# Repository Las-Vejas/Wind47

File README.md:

# Wind47

This is a 60% Ortho linear keyboard, made with Gateron low profile red switches, sk6812mini leds, 2 rotary encoders and a RP2040 Pro Micro.
The keyboard uses a sandwich case, and will probably use QMK for software, but i will do that when i assemble the keyboard.

I made this project to try out making a keyboard, and i wanted to try out an ortholinear keyboard.

I couldn't find a 2U keycap anywhere and im just so done :sob:

## PCB

## Schematic

## Case

- Bottom

- Middle plate

- Top frame

## BOM

| **Quantity** | **Value**                        | **Price** | **Link**                                                                                                                                                                                                                                                                                                                                                                                                                                                                                                                                                                                                                                                                                                                                               |
| ------------ | -------------------------------- | --------- | ------------------------------------------------------------------------------------------------------------------------------------------------------------------------------------------------------------------------------------------------------------------------------------------------------------------------------------------------------------------------------------------------------------------------------------------------------------------------------------------------------------------------------------------------------------------------------------------------------------------------------------------------------------------------------------------------------------------------------------------------------ |
| 5            | Pcb                              | $12.50    | N/A                                                                                                                                                                                                                                                                                                                                                                                                                                                                                                                                                                                                                                                                                                                                                    |
| 47           | Gateron Low Profile Red Switches | $19.10    | [Link](https://www.aliexpress.com/item/1005006870413847.html?spm=a2g0o.cart.0.0.390838daOVG1qw&mp=1&pdp_npi=5%40dis%21USD%21USD%2019.14%21USD%2013.14%21%21USD%2013.14%21%21%21%40211b441e17518077163774247e0c39%2112000038574465209%21ct%21LT%216401819456%21%211%210)                                                                                                                                                                                                                                                                                                                                                                                                                                                                                |
| 47           | Hot Swap Socket                  | $7.21     | [Link](https://www.aliexpress.com/item/1005006042596309.html?spm=a2g0o.detail.0.0.4591LRi5LRi5tJ&mp=1&pdp_npi=5%40dis%21USD%21USD%207.21%21USD%207.21%21%21USD%207.21%21%21%21%40211b441e17518077556815067e0c39%2112000036713923613%21ct%21LT%216401819456%21%211%210)                                                                                                                                                                                                                                                                                                                                                                                                                                                                                 |
| 47           | SK6812MINI LED                   | $3.73     | [Link](https://www.aliexpress.com/item/1005007863635868.html?spm=a2g0o.detail.pcDetailTopMoreOtherSeller.1.677c0nRO0nRO4E&gps-id=pcDetailTopMoreOtherSeller&scm=1007.40050.354490.0&scm_id=1007.40050.354490.0&scm-url=1007.40050.354490.0&pvid=7b6b9416-d88f-40ac-8c6e-72acea23db31&_t=gps-id:pcDetailTopMoreOtherSeller,scm-url:1007.40050.354490.0,pvid:7b6b9416-d88f-40ac-8c6e-72acea23db31,tpp_buckets:668%232846%238113%231998&isseo=y&pdp_ext_f=%7B%22order%22%3A%2258%22%2C%22eval%22%3A%221%22%2C%22sceneId%22%3A%2230050%22%7D&pdp_npi=4%40dis%21USD%213.75%210.99%21%21%213.75%210.99%21%40211b441e17518085375406647e0c46%2112000042594617264%21rec%21LT%216401819456%21ABX&utparam-url=scene%3ApcDetailTopMoreOtherSeller%7Cquery_from%3A) |
| 47           | Diode                            | $1.27     | [Link](https://www.aliexpress.com/item/1005001994794541.html?spm=a2g0o.productlist.main.5.79744b32TWA3jy&aem_p4p_detail=202507060631334743561696551950005639918&algo_pvid=b71027a4-f8cb-4626-8b6c-0d46e56db36f&algo_exp_id=b71027a4-f8cb-4626-8b6c-0d46e56db36f-4&pdp_ext_f=%7B%22order%22%3A%2248%22%2C%22eval%22%3A%221%22%7D&pdp_npi=4%40dis%21USD%211.27%210.99%21%21%211.27%210.99%21%40210156fc17518086930522579eadfd%2112000018351925967%21sea%21LT%216401819456%21ABX&curPageLogUid=3FtGMGt9pZRI&utparam-url=scene%3Asearch%7Cquery_from%3A&search_p4p_id=202507060631334743561696551950005639918_5)                                                                                                                                           |
| 4            | Heatsets                         | $4.01     | [Link](https://www.aliexpress.com/item/1005006838108683.html?spm=a2g0o.cart.0.0.624d38daOi8uPh&mp=1&pdp_npi=5%40dis%21USD%21USD%204.01%21USD%204.01%21%21USD%204.01%21%21%21%40210384cc17518107729603022ec270%2112000038467725089%21ct%21LT%216401819456%21%211%210)                                                                                                                                                                                                                                                                                                                                                                                                                                                                                   |
| 4            | M2.5 x 16 mm screws              | $2.92     | [Link](https://www.aliexpress.com/item/32981974171.html)                                                                                                                                                                                                                                                                                                                                                                                                                                                                                                                                                                                                                                                                                               |
| 2            | RP2040 pro micro                 | $7.08     | [Link](https://www.aliexpress.com/item/1005006130019224.html?spm=a2g0o.cart.0.0.390838daOVG1qw&mp=1&pdp_npi=5%40dis%21USD%21USD%2010.73%21USD%203.54%21%21USD%203.54%21%21%21%40211b441e17518077163774247e0c39%2112000036037945376%21ct%21LT%216401819456%21%211%210)                                                                                                                                                                                                                                                                                                                                                                                                                                                                                  |
| 2            | Rotary Encoder Switch            | $4.02     | [Link](https://www.aliexpress.com/item/32976046900.html?spm=a2g0o.productlist.main.2.6d135ce9p75b8O&algo_pvid=2f2f8c8d-437f-418a-a9cf-3a8994fca321&algo_exp_id=2f2f8c8d-437f-418a-a9cf-3a8994fca321-1&pdp_ext_f=%7B%22order%22%3A%22312%22%2C%22eval%22%3A%221%22%7D&pdp_npi=4%40dis%21USD%214.02%210.99%21%21%214.02%210.99%21%402101062a17518079672848005e14be%2112000025499862671%21sea%21LT%216401819456%21ABX&curPageLogUid=TwSwWdvRutr6&utparam-url=scene%3Asearch%7Cquery_from%3A)                                                                                                                                                                                                                                                              |
| 1            | Keycaps                          | $14.31    | [Link](https://www.aliexpress.com/item/1005004870848679.html?spm=a2g0o.productlist.main.2.20d9kf7mkf7mCx&aem_p4p_detail=2025070606492214374909919118320005194176&algo_pvid=3430a230-6ff9-43e3-a2aa-89966d072dba&algo_exp_id=3430a230-6ff9-43e3-a2aa-89966d072dba-&pdp_ext_f=%7B%22order%22%3A%22302%22%2C%22eval%22%3A%221%22%7D&pdp_npi=4%40dis%21USD%2120.44%2112.07%21%21%2120.44%2112.07%21%40212e509017518097624981576eebc9%2112000033197803002%21sea%21LT%216401819456%21ABX&curPageLogUid=7uruuKe2d5zy&utparam-url=scene%3Asear)                                                                                                                                                                                                                |
| 1            | 2U Stabiliser                    | $2.61     | [Link](https://www.aliexpress.com/item/32864782721.html?spm=a2g0o.cart.0.0.667c38dabvmiJP&mp=1&pdp_npi=5%40dis%21USD%21USD%202.61%21USD%202.61%21%21USD%202.61%21%21%21%40210384cc17518106501267688ec270%2112000033338375131%21ct%21LT%216401819456%21%211%210)                                                                                                                                                                                                                                                                                                                                                                                                                                                                                        |
| 1            | Hex wrench                       | $2.47     | [Link](https://www.aliexpress.com/item/1005005430749401.html?spm=a2g0o.cart.0.0.624d38daOi8uPh&mp=1&pdp_npi=5%40dis%21USD%21USD%207.28%21USD%202.47%21%21USD%202.47%21%21%21%402103849717518141207421645eadef%2112000033040817269%21ct%21LT%216401819456%21%211%210)                                                                                                                                                                                                                                                                                                                                                                                                                                                                                   |
|              | **Total:**                       | $88.68    |                                                                                                                                                                                                                                                                                                                                                                                                                                                                                                                                                                                                                                                                                                                                                        |
|              | Aliexpress Shipping              | $7.45     | N/A                                                                                                                                                                                                                                                                                                                                                                                                                                                                                                                                                                                                                                                                                                                                                    |

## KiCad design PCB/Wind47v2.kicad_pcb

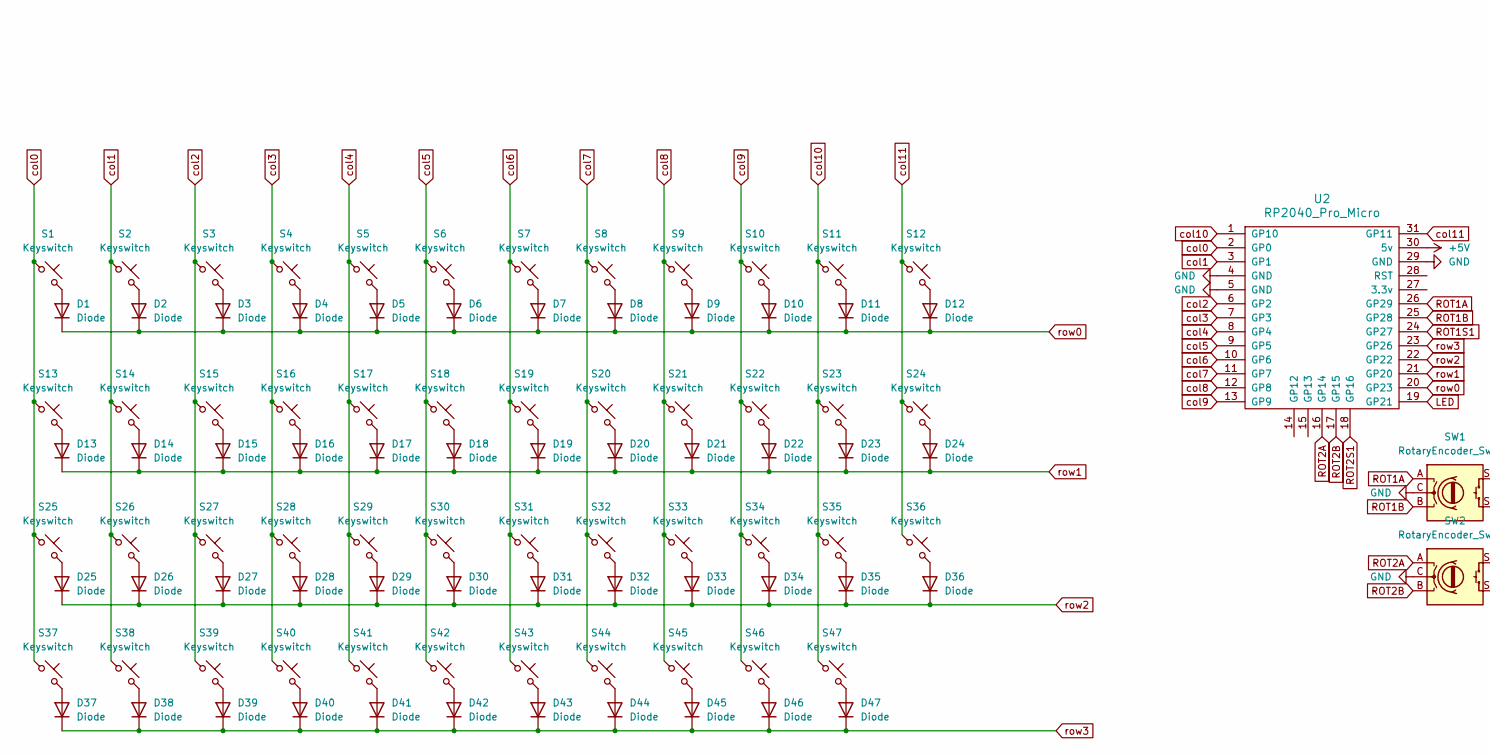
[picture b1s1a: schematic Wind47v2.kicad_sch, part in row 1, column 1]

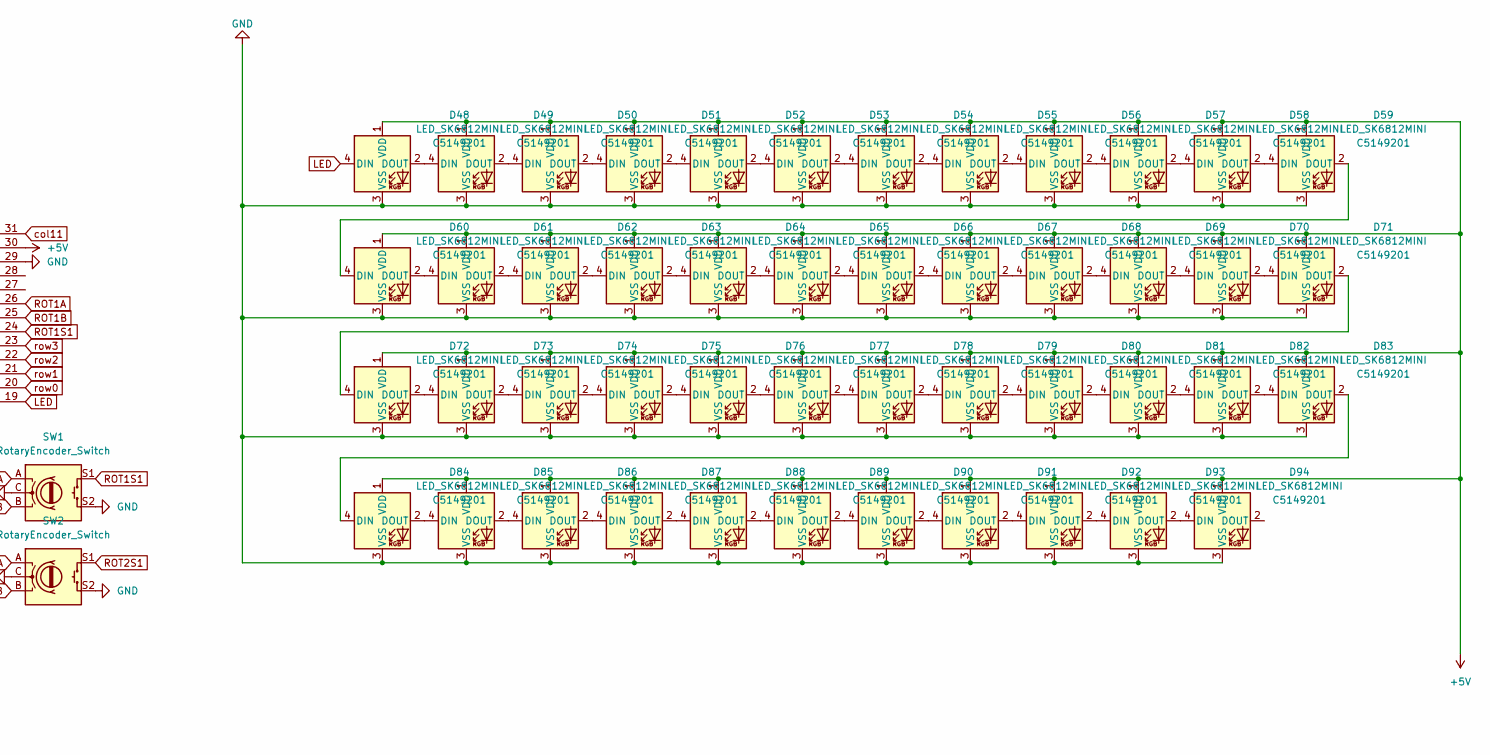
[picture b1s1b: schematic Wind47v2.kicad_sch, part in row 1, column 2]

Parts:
D1, D2, D3, D4, D5, D6, D7, D8, D9, D10, D11, D12, D13, D14, D15, D16, D17, D18, D19, D20, D21, D22, D23, D24, D25, D26, D27, D28, D29, D30, D31, D32, D33, D34, D35, D36, D37, D38, D39, D40, D41, D42, D43, D44, D45, D46, D47: Diode; D_SOD-123
D48, D49, D50, D51, D52, D53, D54, D55, D56, D57, D58, D59, D60, D61, D62, D63, D64, D65, D66, D67, D68, D69, D70, D71, D72, D73, D74, D75, D76, D77, D78, D79, D80, D81, D82, D83, D84, D85, D86, D87, D88, D89, D90, D91, D92, D93, D94: LED_SK6812MINI; LCSC C5149201
S1, S2, S3, S4, S5, S6, S7, S8, S9, S10, S11, S12, S13, S14, S15, S16, S17, S18, S19, S20, S21, S22, S23, S24, S25, S26, S27, S28, S29, S30, S31, S32, S33, S34, S35, S36, S37, S38, S39, S40, S41, S42, S43, S44, S45, S46, S47: Keyswitch; SW_Gateron_LowProfile_HotSwap_PTH
SW1, SW2: RotaryEncoder_Switch; RotaryEncoder_Alps_EC11E-Switch_Vertical_H20mm_CircularMoun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
U2: RP2040_Pro_Micro

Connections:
+5V: D48.1 (VDD), D49.1 (VDD), D50.1 (VDD), D51.1 (VDD), D52.1 (VDD), D53.1 (VDD), D54.1 (VDD), D55.1 (VDD), D56.1 (VDD), D57.1 (VDD), D58.1 (VDD), D59.1 (VDD), D60.1 (VDD), D61.1 (VDD), D62.1 (VDD), D63.1 (VDD), D64.1 (VDD), D65.1 (VDD), D66.1 (VDD), D67.1 (VDD), D68.1 (VDD), D69.1 (VDD), D70.1 (VDD), D71.1 (VDD), D72.1 (VDD), D73.1 (VDD), D74.1 (VDD), D75.1 (VDD), D76.1 (VDD), D77.1 (VDD), D78.1 (VDD), D79.1 (VDD), D80.1 (VDD), D81.1 (VDD), D82.1 (VDD), D83.1 (VDD), D84.1 (VDD), D85.1 (VDD), D86.1 (VDD), D87.1 (VDD), D88.1 (VDD), D89.1 (VDD), D90.1 (VDD), D91.1 (VDD), D92.1 (VDD), D93.1 (VDD), D94.1 (VDD), U2.30 (5v)
GND: D48.3 (VSS), D49.3 (VSS), D50.3 (VSS), D51.3 (VSS), D52.3 (VSS), D53.3 (VSS), D54.3 (VSS), D55.3 (VSS), D56.3 (VSS), D57.3 (VSS), D58.3 (VSS), D59.3 (VSS), D60.3 (VSS), D61.3 (VSS), D62.3 (VSS), D63.3 (VSS), D64.3 (VSS), D65.3 (VSS), D66.3 (VSS), D67.3 (VSS), D68.3 (VSS), D69.3 (VSS), D70.3 (VSS), D71.3 (VSS), D72.3 (VSS), D73.3 (VSS), D74.3 (VSS), D75.3 (VSS), D76.3 (VSS), D77.3 (VSS), D78.3 (VSS), D79.3 (VSS), D80.3 (VSS), D81.3 (VSS), D82.3 (VSS), D83.3 (VSS), D84.3 (VSS), D85.3 (VSS), D86.3 (VSS), D87.3 (VSS), D88.3 (VSS), D89.3 (VSS), D90.3 (VSS), D91.3 (VSS), D92.3 (VSS), D93.3 (VSS), D94.3 (VSS), SW1.C, SW1.S2, SW2.C, SW2.S2, U2.4 (GND), U2.5 (GND), U2.29 (GND)
LED: D48.4 (DIN), U2.19 (GP21)
unnamed: D1.2 (A), S1.2
unnamed: D2.2 (A), S2.2
unnamed: D3.2 (A), S3.2
unnamed: D4.2 (A), S4.2
unnamed: D5.2 (A), S5.2
unnamed: D6.2 (A), S6.2
unnamed: D7.2 (A), S7.2
unnamed: D8.2 (A), S8.2
unnamed: D9.2 (A), S9.2
unnamed: D10.2 (A), S10.2
unnamed: D11.2 (A), S11.2
unnamed: D12.2 (A), S12.2
unnamed: D13.2 (A), S13.2
unnamed: D14.2 (A), S14.2
unnamed: D15.2 (A), S15.2
unnamed: D16.2 (A), S16.2
unnamed: D17.2 (A), S17.2
unnamed: D18.2 (A), S18.2
unnamed: D19.2 (A), S19.2
unnamed: D20.2 (A), S20.2
unnamed: D21.2 (A), S21.2
unnamed: D22.2 (A), S22.2
unnamed: D23.2 (A), S23.2
unnamed: D24.2 (A), S24.2
unnamed: D25.2 (A), S25.2
unnamed: D26.2 (A), S26.2
unnamed: D27.2 (A), S27.2
unnamed: D28.2 (A), S28.2
unnamed: D29.2 (A), S29.2
unnamed: D30.2 (A), S30.2
unnamed: D31.2 (A), S31.2
unnamed: D32.2 (A), S32.2
unnamed: D33.2 (A), S33.2
unnamed: D34.2 (A), S34.2
unnamed: D35.2 (A), S35.2
unnamed: D36.2 (A), S36.2
unnamed: D37.2 (A), S37.2
unnamed: D38.2 (A), S38.2
unnamed: D39.2 (A), S39.2
unnamed: D40.2 (A), S40.2
unnamed: D41.2 (A), S41.2
unnamed: D42.2 (A), S42.2
unnamed: D43.2 (A), S43.2
unnamed: D44.2 (A), S44.2
unnamed: D45.2 (A), S45.2
unnamed: D46.2 (A), S46.2
unnamed: D47.2 (A), S47.2
unnamed: D48.2 (DOUT), D49.4 (DIN)
unnamed: D49.2 (DOUT), D50.4 (DIN)
unnamed: D50.2 (DOUT), D51.4 (DIN)
unnamed: D51.2 (DOUT), D52.4 (DIN)
unnamed: D52.2 (DOUT), D53.4 (DIN)
unnamed: D53.2 (DOUT), D54.4 (DIN)
unnamed: D54.2 (DOUT), D55.4 (DIN)
unnamed: D55.2 (DOUT), D56.4 (DIN)
unnamed: D56.2 (DOUT), D57.4 (DIN)
unnamed: D57.2 (DOUT), D58.4 (DIN)
unnamed: D58.2 (DOUT), D59.4 (DIN)
unnamed: D59.2 (DOUT), D60.4 (DIN)
unnamed: D60.2 (DOUT), D61.4 (DIN)
unnamed: D61.2 (DOUT), D62.4 (DIN)
unnamed: D62.2 (DOUT), D63.4 (DIN)
unnamed: D63.2 (DOUT), D64.4 (DIN)
unnamed: D64.2 (DOUT), D65.4 (DIN)
unnamed: D65.2 (DOUT), D66.4 (DIN)
unnamed: D66.2 (DOUT), D67.4 (DIN)
unnamed: D67.2 (DOUT), D68.4 (DIN)
unnamed: D68.2 (DOUT), D69.4 (DIN)
unnamed: D69.2 (DOUT), D70.4 (DIN)
unnamed: D70.2 (DOUT), D71.4 (DIN)
unnamed: D71.2 (DOUT), D72.4 (DIN)
unnamed: D72.2 (DOUT), D73.4 (DIN)
unnamed: D73.2 (DOUT), D74.4 (DIN)
unnamed: D74.2 (DOUT), D75.4 (DIN)
unnamed: D75.2 (DOUT), D76.4 (DIN)
unnamed: D76.2 (DOUT), D77.4 (DIN)
unnamed: D77.2 (DOUT), D78.4 (DIN)
unnamed: D78.2 (DOUT), D79.4 (DIN)
unnamed: D79.2 (DOUT), D80.4 (DIN)
unnamed: D80.2 (DOUT), D81.4 (DIN)
unnamed: D81.2 (DOUT), D82.4 (DIN)
unnamed: D82.2 (DOUT), D83.4 (DIN)
unnamed: D83.2 (DOUT), D84.4 (DIN)
unnamed: D84.2 (DOUT), D85.4 (DIN)
unnamed: D85.2 (DOUT), D86.4 (DIN)
unnamed: D86.2 (DOUT), D87.4 (DIN)
unnamed: D87.2 (DOUT), D88.4 (DIN)
unnamed: D88.2 (DOUT), D89.4 (DIN)
unnamed: D89.2 (DOUT), D90.4 (DIN)
unnamed: D90.2 (DOUT), D91.4 (DIN)
unnamed: D91.2 (DOUT), D92.4 (DIN)
unnamed: D92.2 (DOUT), D93.4 (DIN)
unnamed: D93.2 (DOUT), D94.4 (DIN)
ROT1A: SW1.A, U2.26 (GP29)
ROT1B: SW1.B, U2.25 (GP28)
ROT1S1: SW1.S1, U2.24 (GP27)
ROT2A: SW2.A, U2.16 (GP14)
ROT2B: SW2.B, U2.17 (GP15)
ROT2S1: SW2.S1, U2.18 (GP16)
col0: S1.1, S13.1, S25.1, S37.1, U2.2 (GP0)
col1: S2.1, S14.1, S26.1, S38.1, U2.3 (GP1)
col2: S3.1, S15.1, S27.1, S39.1, U2.6 (GP2)
col3: S4.1, S16.1, S28.1, S40.1, U2.7 (GP3)
col4: S5.1, S17.1, S29.1, S41.1, U2.8 (GP4)
col5: S6.1, S18.1, S30.1, S42.1, U2.9 (GP5)
col6: S7.1, S19.1, S31.1, S43.1, U2.10 (GP6)
col7: S8.1, S20.1, S32.1, S44.1, U2.11 (GP7)
col8: S9.1, S21.1, S33.1, S45.1, U2.12 (GP8)
col9: S10.1, S22.1, S34.1, S46.1, U2.13 (GP9)
col10: S11.1, S23.1, S35.1, S47.1, U2.1 (GP10)
col11: S12.1, S24.1, S36.1, U2.31 (GP11)
row0: D1.1 (K), D2.1 (K), D3.1 (K), D4.1 (K), D5.1 (K), D6.1 (K), D7.1 (K), D8.1 (K), D9.1 (K), D10.1 (K), D11.1 (K), D12.1 (K), U2.20 (GP23)
row1: D13.1 (K), D14.1 (K), D15.1 (K), D16.1 (K), D17.1 (K), D18.1 (K), D19.1 (K), D20.1 (K), D21.1 (K), D22.1 (K), D23.1 (K), D24.1 (K), U2.21 (GP20)
row2: D25.1 (K), D26.1 (K), D27.1 (K), D28.1 (K), D29.1 (K), D30.1 (K), D31.1 (K), D32.1 (K), D33.1 (K), D34.1 (K), D35.1 (K), D36.1 (K), U2.22 (GP22)
row3: D37.1 (K), D38.1 (K), D39.1 (K), D40.1 (K), D41.1 (K), D42.1 (K), D43.1 (K), D44.1 (K), D45.1 (K), D46.1 (K), D47.1 (K), U2.23 (GP26)

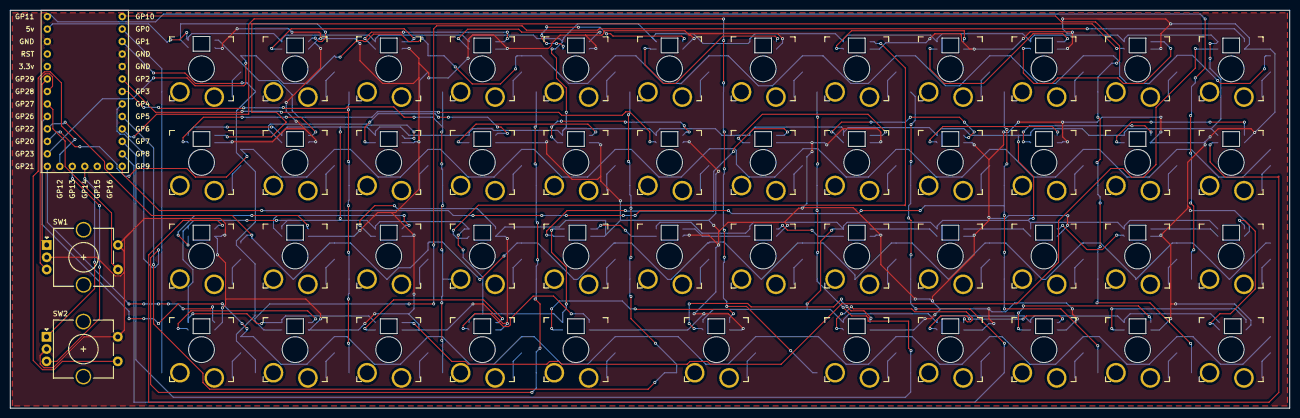
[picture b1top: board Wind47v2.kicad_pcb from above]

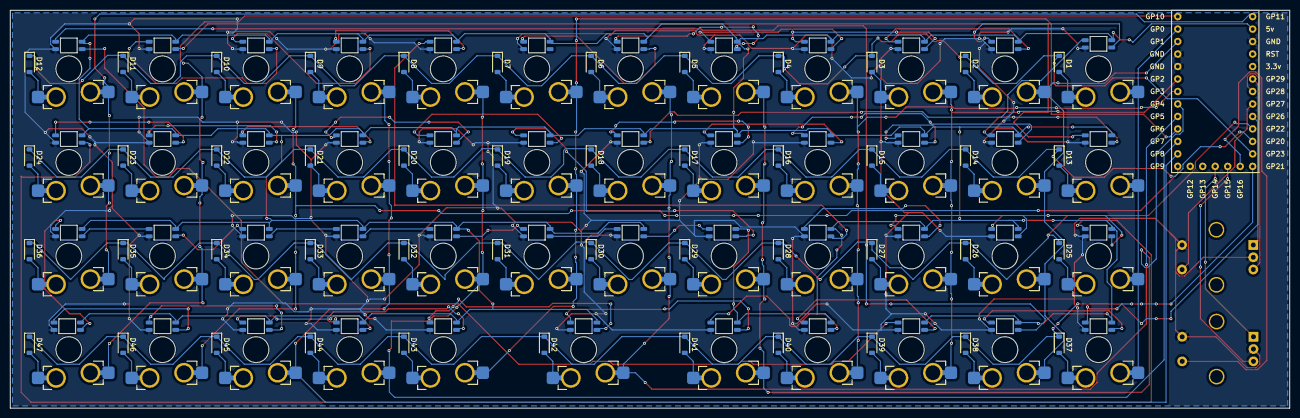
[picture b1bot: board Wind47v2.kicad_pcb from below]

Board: 2 copper layers, 260.4 x 81.0 mm, 144 parts (95 on the bottom side), 118 nets.

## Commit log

2025-07-03 Started and almost finished the schem
2025-07-04 Initial commit
    Add initial project files and setup.
2025-07-04 add layouts
2025-07-06 a lot of work
2025-07-06 update gerbers
2025-07-06 update kicad files
2025-07-06 rename kicad files
2025-07-06 added firmware. idk if it works
2025-07-06 more work idk
2025-07-07 Updated step file
2025-07-07 Rename Wind47-pcb (~recovered).zip to CAD/Wind47-pcb (~recovered).zip
2025-07-08 Headache
2025-07-10 Update PCB net assignments and production files
    Renamed and reordered several net assignments in Wind47v2.kicad_pcb to remove unused nets and improve clarity. Updated production STL and ZIP files, removed outdated backups, and added new 3D and PCB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
2025-07-10 Update bottom case image
2025-07-10 Update BOM
